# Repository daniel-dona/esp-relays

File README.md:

# esp-relays
Hardware y software para un controlador IoT de persianas motorizadas

## Hardware
### PCB
### ESP12 module

## Software
### NodeMCU
### Lua

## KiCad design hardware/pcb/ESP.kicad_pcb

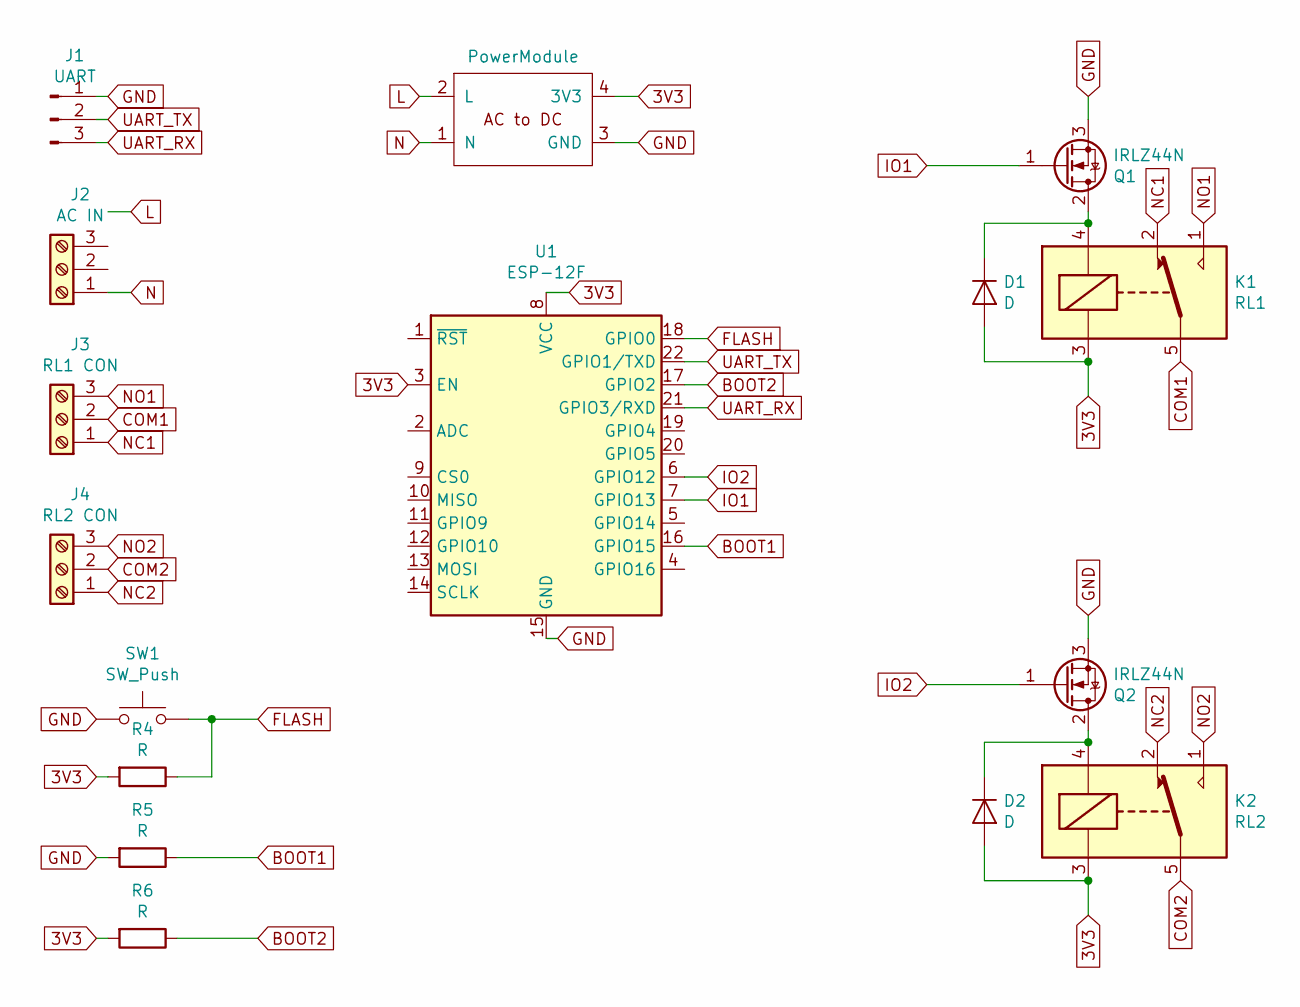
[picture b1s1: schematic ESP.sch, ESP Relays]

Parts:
D1, D2: D; D_DO-35_SOD27_P7.62mm_Horizontal
J1: UART; PinHeader_1x03_P2.54mm_Vertical
J2: AC IN; TerminalBlock_Altech_AK300-3_P5.00mm
J3: RL1 CON; TerminalBlock_Altech_AK300-3_P5.00mm
J4: RL2 CON; TerminalBlock_Altech_AK300-3_P5.00mm
K1: RL1; Relay_SPDT_SANYOU_SRD_Series_Form_C
K2: RL2; Relay_SPDT_SANYOU_SRD_Series_Form_C
PW101: PowerModule
Q1, Q2: IRLZ44N; TO-220-3_Vertical
R4, R5, R6: R; R_Axial_DIN0204_L3.6mm_D1.6mm_P7.62mm_Horizontal
SW1: SW_Push; SW_PUSH_6mm
U1: ESP-12F; ESP-12E

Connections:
3V3: D1.2 (A), D2.2 (A), K1.3, K2.3, PW101.4 (3V3), R4.2, R6.2, U1.3 (EN), U1.8 (VCC)
BOOT1: R5.1, U1.16 (GPIO15)
BOOT2: R6.1, U1.17 (GPIO2)
COM1: J3.2, K1.5
COM2: J4.2, K2.5
FLASH: R4.1, SW1.2, U1.18 (GPIO0)
GND: J1.1, PW101.3 (GND), Q1.3 (S), Q2.3 (S), R5.2, SW1.1, U1.15 (GND)
IO1: Q1.1 (G), U1.7 (GPIO13)
IO2: Q2.1 (G), U1.6 (GPIO12)
L: J2.3, PW101.2 (L)
N: J2.1, PW101.1 (N)
NC1: J3.1, K1.2
NC2: J4.1, K2.2
NO1: J3.3, K1.1
NO2: J4.3, K2.1
unnamed: D1.1 (K), K1.4, Q1.2 (D)
unnamed: D2.1 (K), K2.4, Q2.2 (D)
UART_RX: J1.3, U1.21 (GPIO3/RXD)
UART_TX: J1.2, U1.22 (GPIO1/TXD)

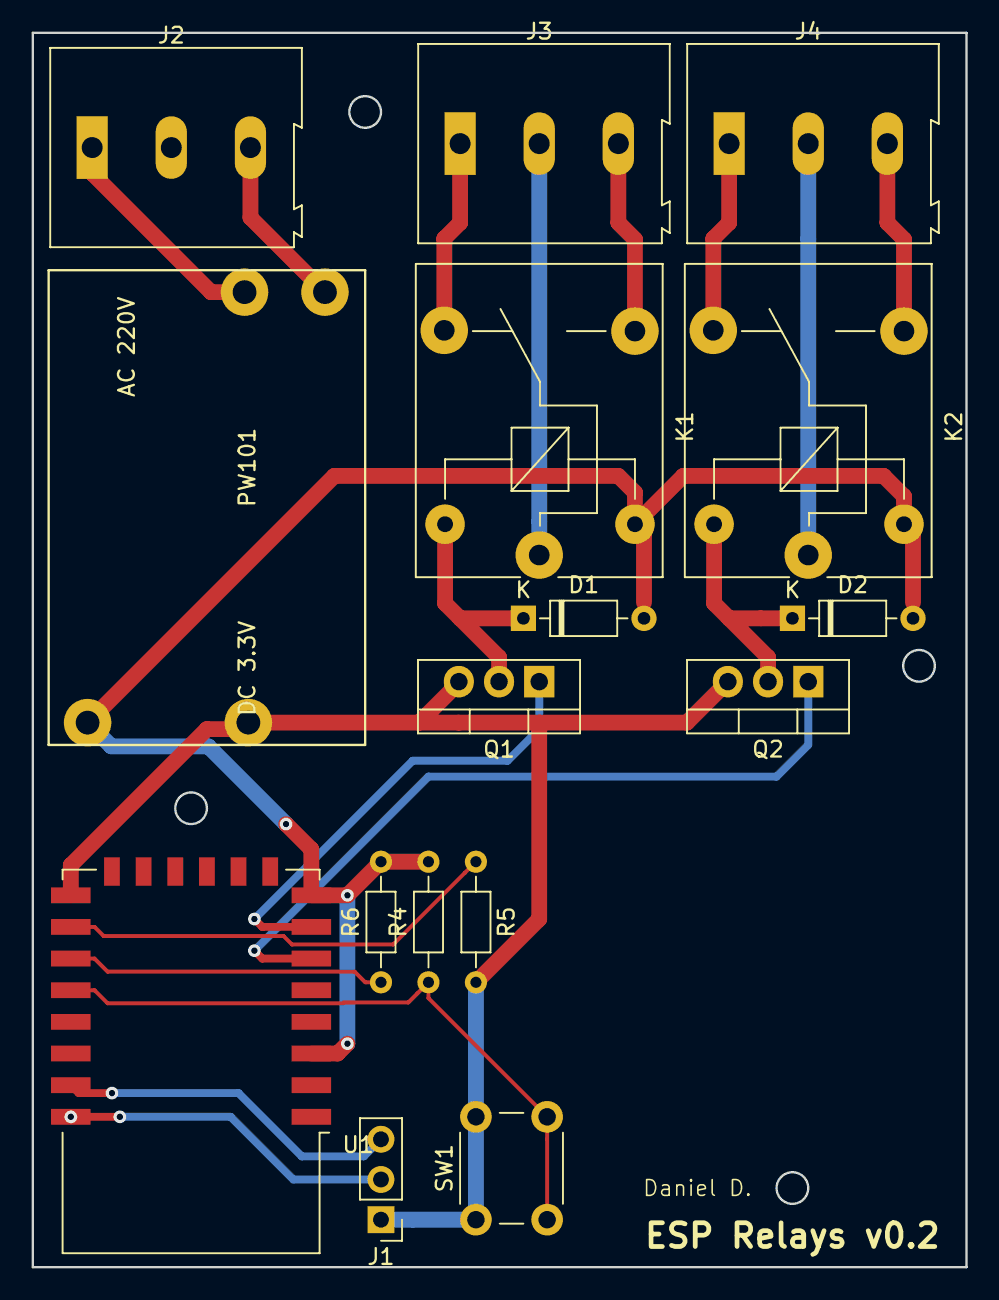
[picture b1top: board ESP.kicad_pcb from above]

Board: 2 copper layers, 59.0 x 78.0 mm, 16 parts (0 on the bottom side), 19 nets.

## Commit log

2019-08-19 Init
2020-10-20 Fix reboot-as-solution behavior
2020-10-20 Is this the good time?

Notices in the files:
hardware/pcb/ESP.sch:
Licensed under GNU GPL v3
